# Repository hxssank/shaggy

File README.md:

# Shaggy

A physical music controller built around Raspberry Pi Pico 2. Nine Hall-sensor tiles bring individual audio stems in and out of a mix. A rotary control handles volume and library selection, and a small LCD shows the current bank and active stems.

The player starts all voices under a paused I2S stream, changes gains during playback, and admits a cached bank only after WAV and hash checks. [The engineering walkthrough](ENGINEERING.md) traces playback timing and the separate recovery bank.

This repository contains CircuitPython firmware, host-side preparation and installation tools, tests, and a KiCad carrier-board design. Audio recordings and device-specific backups are excluded.

## Open the carrier-board files

| File | Contents |
| --- | --- |
| [Schematic PDF](hardware/pcb/reports/schematic.pdf) and [KiCad schematic](hardware/pcb/shaggy-carrier.kicad_sch) | Pico, Hall-sensor, display, DAC and microSD connections |
| [KiCad board](hardware/pcb/shaggy-carrier.kicad_pcb) and [top view](hardware/pcb/preview/shaggy-top.png) | 100 x 80 mm revision A carrier |
| [Board STEP](hardware/pcb/shaggy-carrier.step) and [3D view](hardware/pcb/preview/shaggy-3d.png) | Carrier geometry for mechanical review |
| [BOM](hardware/pcb/bom.csv) | Component references, quantities and footprints |
| [Cable pinout](hardware/pcb/cable-pinout.csv) | Connector pin numbers, nets and wire labels |
| [Gerbers and drills](hardware/pcb/fabrication-prototype/) | Revision A prototype fabrication exports |
| [DRC report](hardware/pcb/reports/pcb-drc.json) | Current board check, including the configured exclusions |

KiCad 10.0.7 reported zero violations, unconnected items or schematic-parity issues on November 9. The report lists six disabled checks, including missing courtyards and footprint-filter mismatches. Review those exclusions and the actual module pinouts before ordering a PCB. No fabricated carrier test is recorded.

## What works in the code

- Nine stem controls with time-based fades and debounced sensor state.
- SD-card libraries with validated manifests and up to 64 banks.
- Flash caching before playback, so active voices do not compete with the display for SD bandwidth.
- An internal House-bank recovery path when the SD card or library fails.
- Volume takeover, hold gestures and a library picker on a 240 x 280 display.
- Staged installation with file hashes, readback checks, backups and rollback paths.

```mermaid
flowchart LR
  Tiles[Hall-sensor tiles] --> Control[Stem and volume control]
  Knob[Rotary control] --> Control
  SD[SD library] --> Manifest[Manifest validation]
  Manifest --> Cache[Selected-bank flash cache]
  Cache --> Player[Nine-voice player]
  Control --> Player
  Player --> DAC[TLV320DAC3100 DAC]
  DAC --> Speaker[Speaker]
  Control --> Display[ST7789 display]
```

## Engineering decisions

The SD card and display share SPI. Loading a bank into flash before playback avoids asking that bus to sustain every audio stream while redrawing the UI. `bank_cache.py` verifies WAV structure and available space before activating a cached bank.

The installer treats partial writes as a failure. It stages replacements, verifies content, and retains the prior files until activation succeeds. The tests inject write and reconnect failures to check the rollback path.

## Source map

| Path | Responsibility |
| --- | --- |
| [`firmware/shaggy_os.py`](firmware/shaggy_os.py) | Library startup, selected bank, recovery and playback sessions |
| [`firmware/shaggy.py`](firmware/shaggy.py) | Pico GPIO, audio mixer and playback loop |
| [`firmware/bank_cache.py`](firmware/bank_cache.py) | Validated SD-to-flash bank caching |
| [`firmware/player_display.py`](firmware/player_display.py) | Bank, stem, volume and error display |
| [`tools/prepare_sd_library.py`](tools/prepare_sd_library.py) | WAV validation, resampling and aligned SD library output |
| [`tools/install_sd.py`](tools/install_sd.py) | Staged firmware/library deployment and recovery |
| [`hardware/pcb/`](hardware/pcb/) | Carrier-board sources, footprint definitions and design scripts |
| [`tests/`](tests/) | Host-side logic and failure-injection tests |

## Run the host tests

Use Python 3.13 or 3.14 and [uv](https://docs.astral.sh/uv/).

```sh
uv sync --group dev
uv run pytest -q
uv run ruff check firmware tools tests
```

The public source snapshot passed **568 tests on November 9, 2026**. Two optional resampling tests skipped because NumPy was absent from that environment. A separate carrier-board netlist suite passed 11 tests. Ruff passed for firmware, tools and tests. These tests use fake hardware interfaces; they do not establish timing or audio quality on a physical Pico.

## Hardware and audio setup

The implementation targets a Pico 2 running CircuitPython, a TLV320DAC3100 audio board, an ST7789 display, nine Hall sensors, a volume potentiometer and an SPI microSD reader. Pin assignments live in `firmware/shaggy.py`, `firmware/sd_storage.py` and `firmware/volume_test.py`. Confirm power rails and actual module pinouts before wiring.

Supply your own licensed audio. Each bank uses nine mono, 16-bit PCM WAV files with matching frame counts. The SD preparation path produces 22,050 Hz files and validates the bank before deployment. The runtime and tests do not require redistributing the original recordings.

Run `python tools/install_sd.py --help` before connecting a board. Device installation writes firmware and storage; the desktop test command above does not open a physical device.

## Current limits and next work

The carrier PCB is a prototype design. A passing software suite or KiCad check does not prove a fabricated board works. The next hardware checks are long-duration playback with all nine stems, bank changes under realistic card latency, power-cycle recovery and end-to-end wiring review.

The public suite excludes acceptance tests that depended on private audio recordings. General WAV, manifest, caching and installation tests generate their own fixtures.

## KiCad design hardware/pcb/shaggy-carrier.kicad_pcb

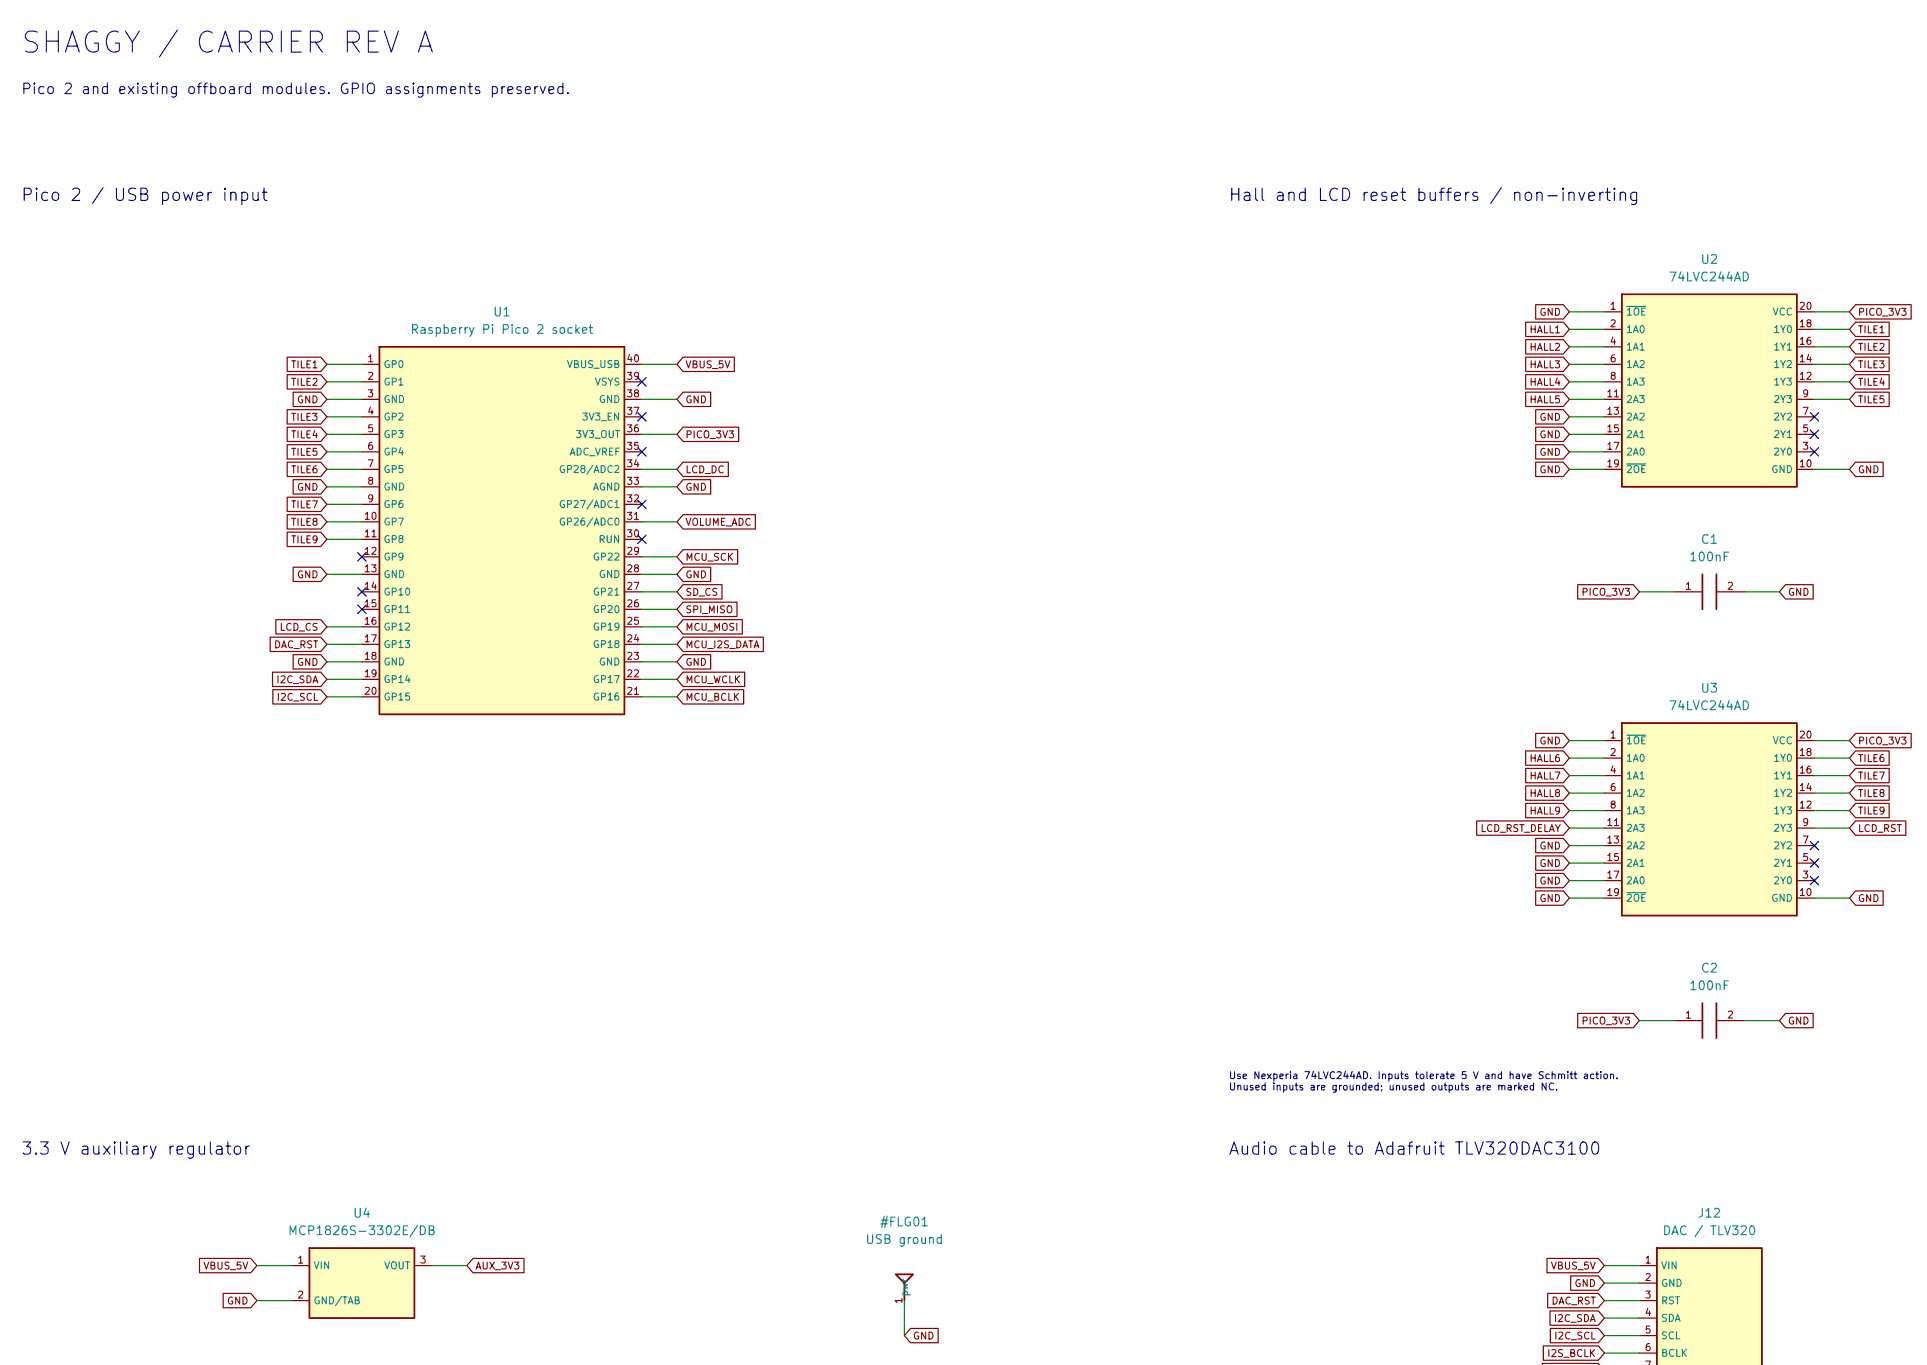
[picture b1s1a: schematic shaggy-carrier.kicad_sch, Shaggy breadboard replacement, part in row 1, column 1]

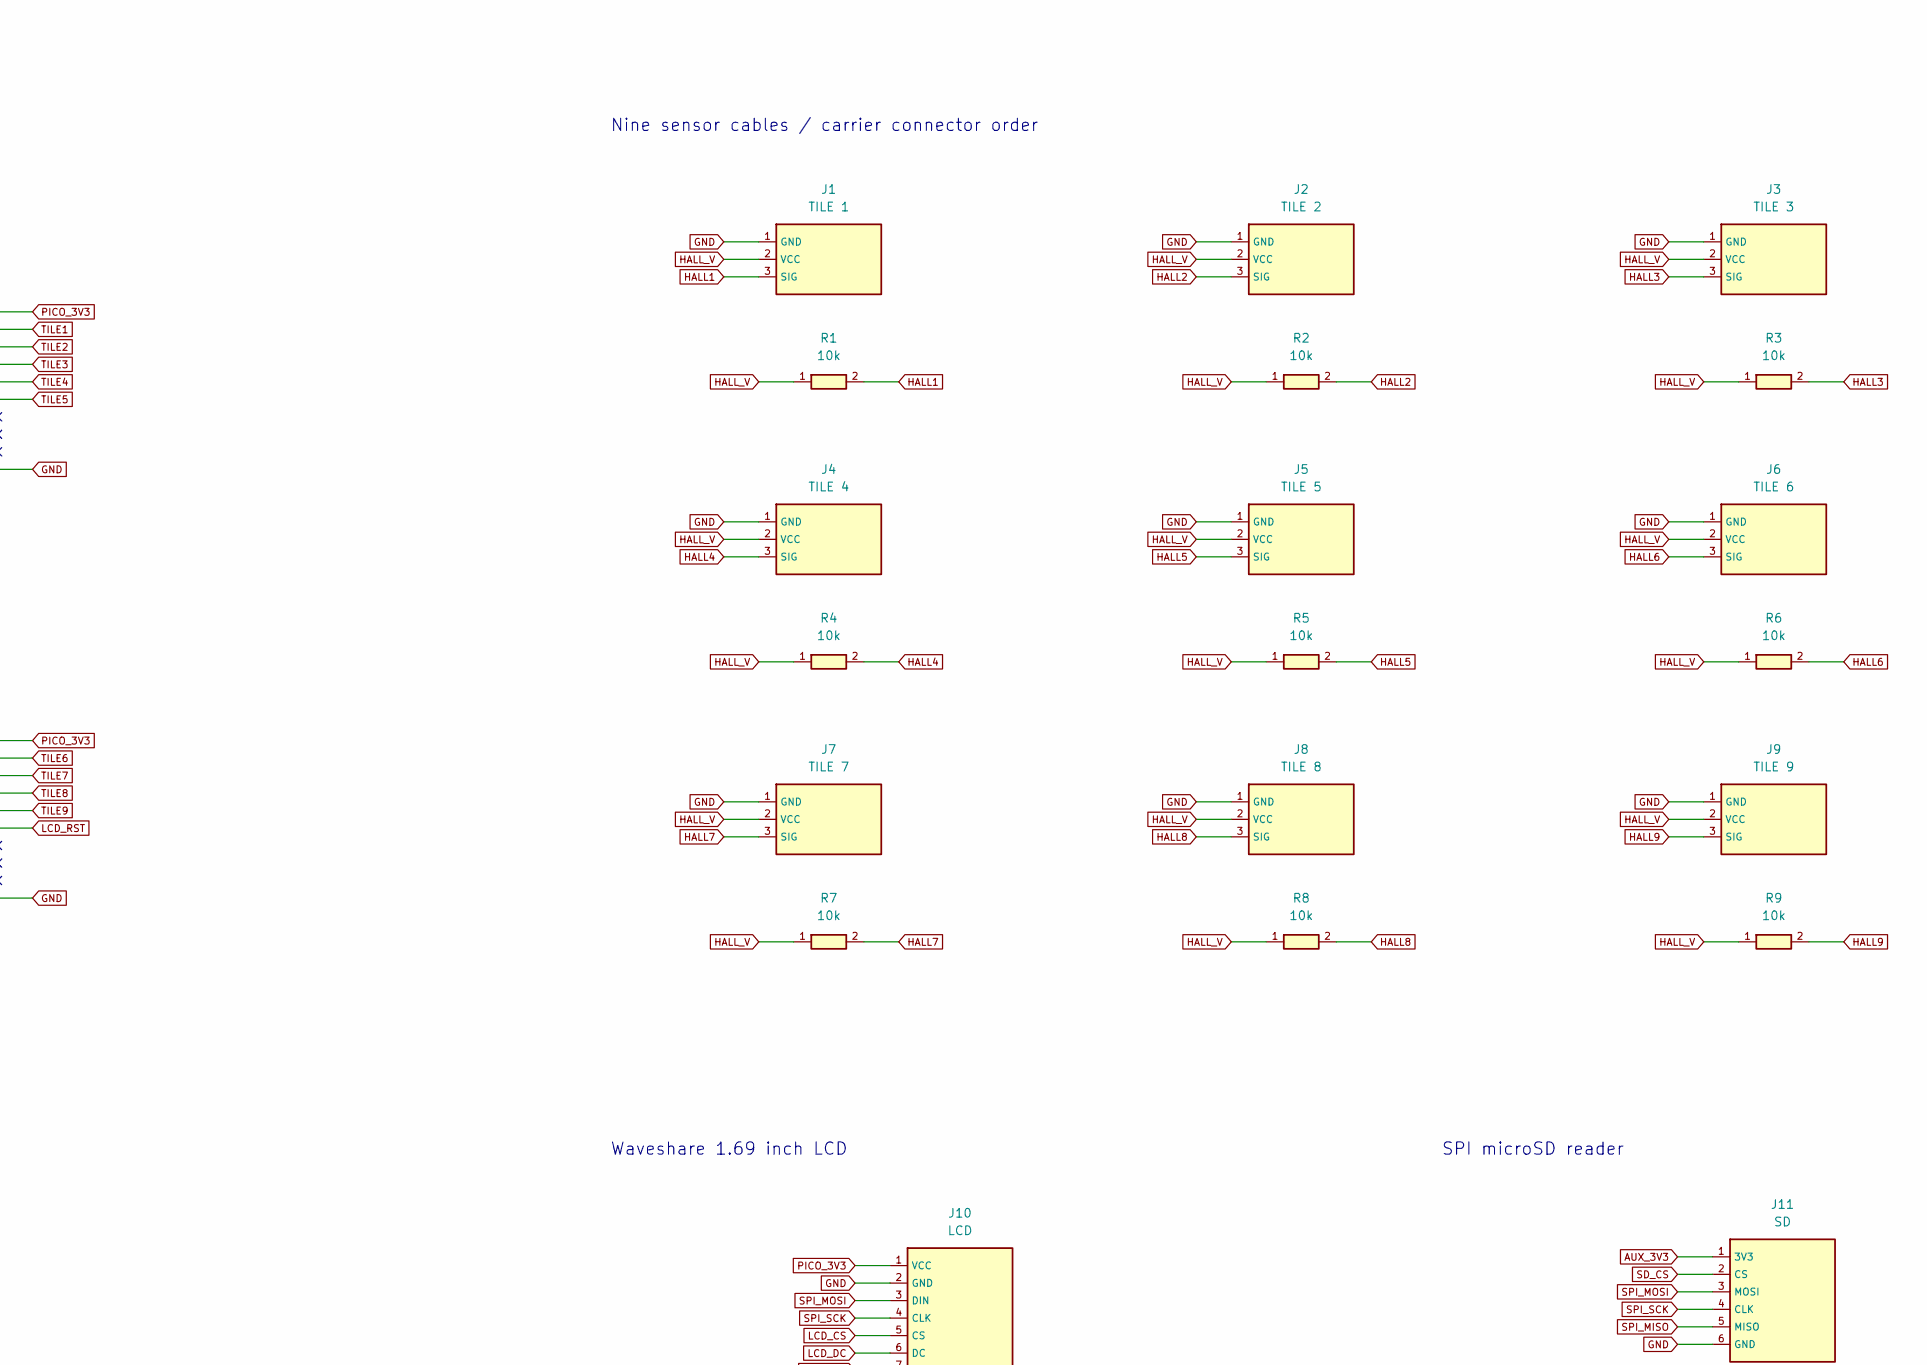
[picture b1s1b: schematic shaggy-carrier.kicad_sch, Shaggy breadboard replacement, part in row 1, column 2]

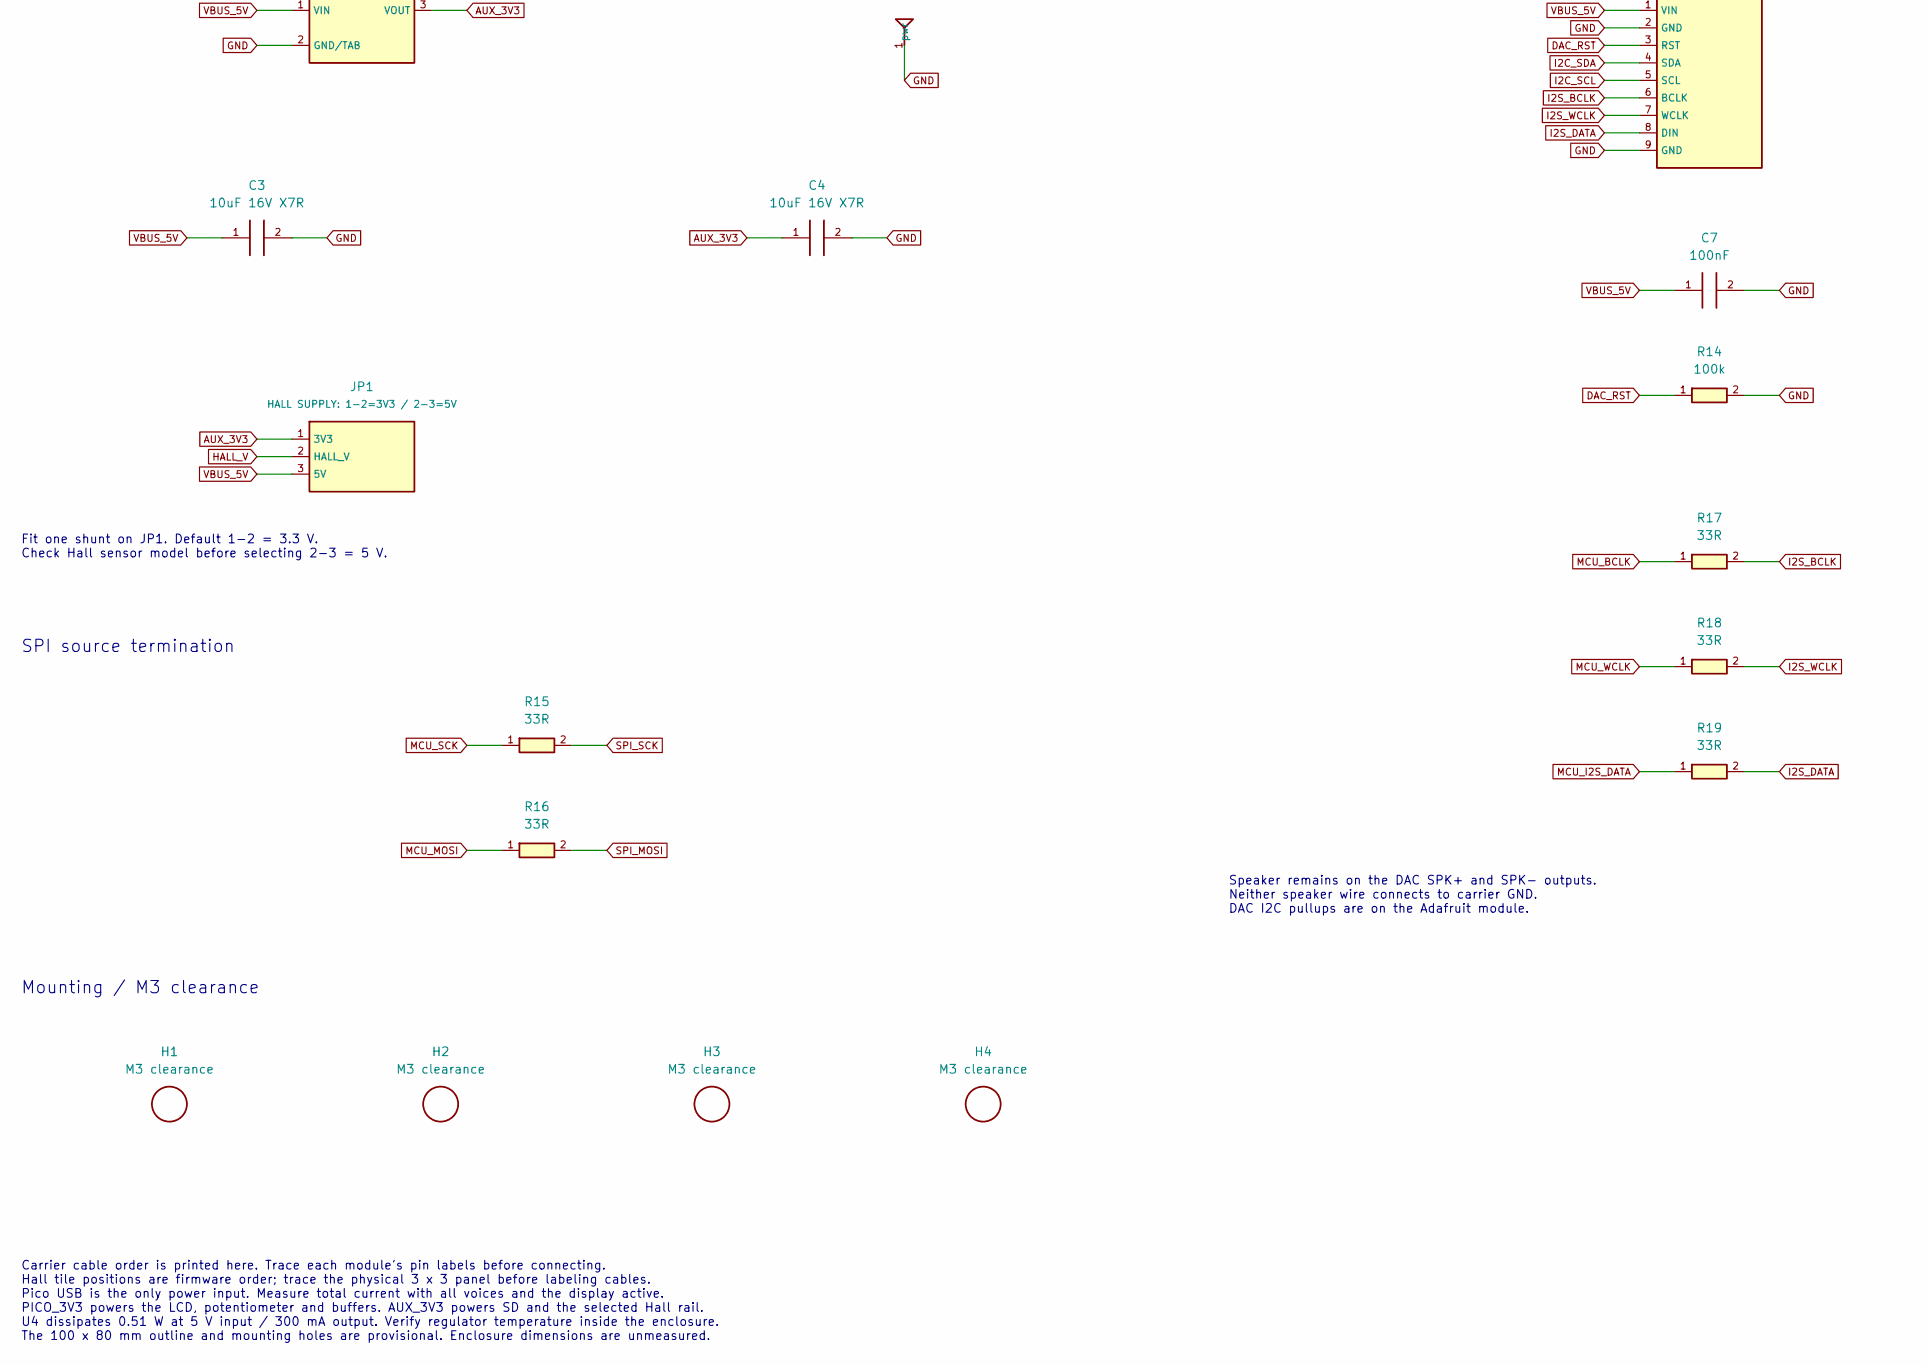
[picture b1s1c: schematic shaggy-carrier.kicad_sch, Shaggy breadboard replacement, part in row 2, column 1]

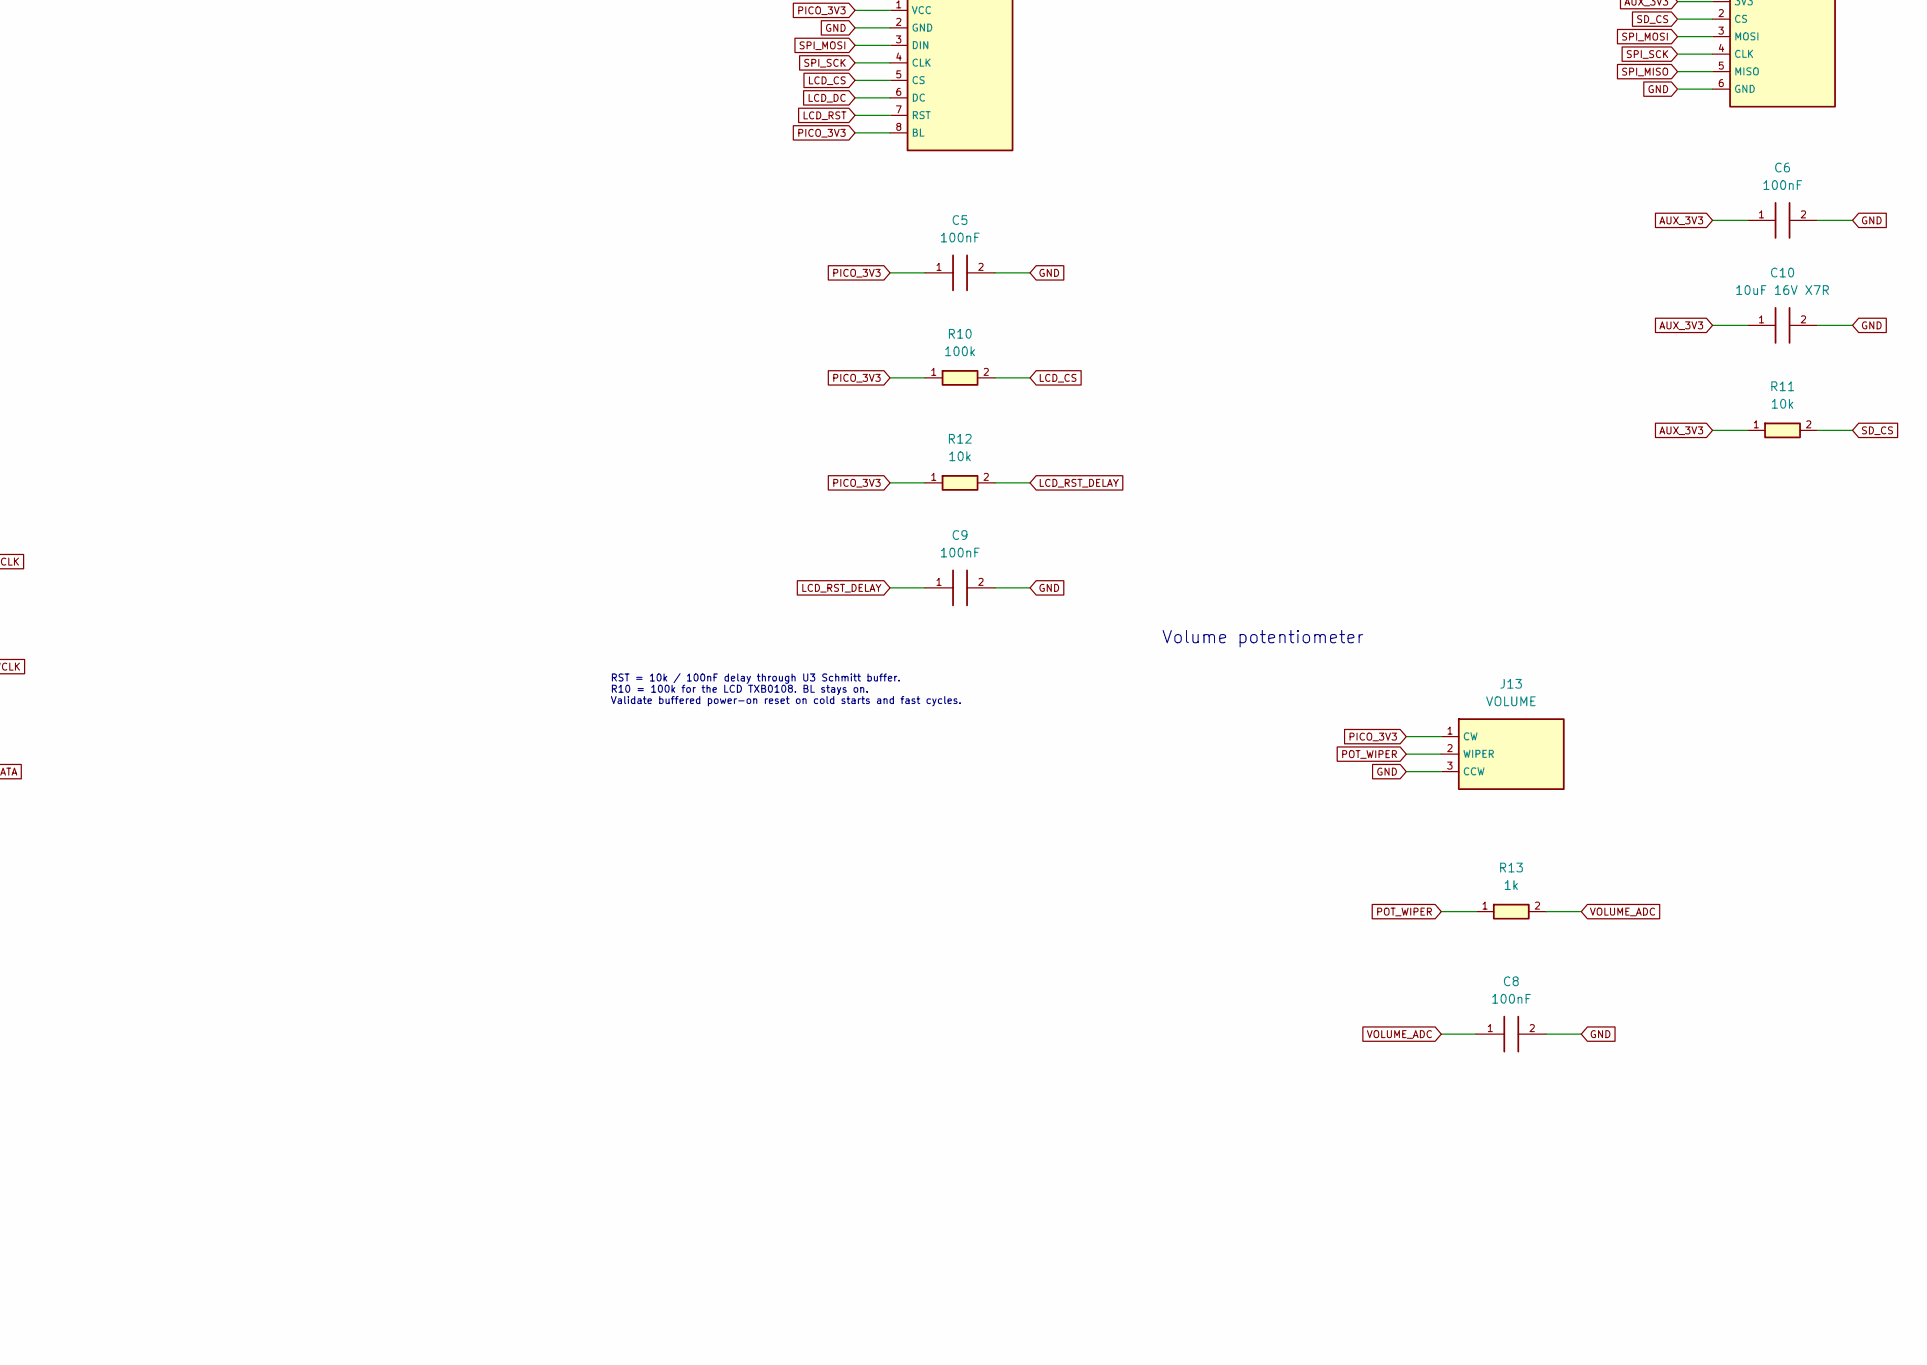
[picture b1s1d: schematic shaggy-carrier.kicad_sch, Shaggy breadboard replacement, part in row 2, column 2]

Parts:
C1, C2, C5, C6, C7, C8, C9: 100nF; C_0805_2012Metric
C3, C4, C10: 10uF 16V X7R; C_0805_2012Metric
H1, H2, H3, H4: M3 clearance; MountingHole_3.2mm_M3
J1: TILE 1; JST_XH_B3B-XH-A_1x03_P2.50mm_Vertical
J2: TILE 2; JST_XH_B3B-XH-A_1x03_P2.50mm_Vertical
J3: TILE 3; JST_XH_B3B-XH-A_1x03_P2.50mm_Vertical
J4: TILE 4; JST_XH_B3B-XH-A_1x03_P2.50mm_Vertical
J5: TILE 5; JST_XH_B3B-XH-A_1x03_P2.50mm_Vertical
J6: TILE 6; JST_XH_B3B-XH-A_1x03_P2.50mm_Vertical
J7: TILE 7; JST_XH_B3B-XH-A_1x03_P2.50mm_Vertical
J8: TILE 8; JST_XH_B3B-XH-A_1x03_P2.50mm_Vertical
J9: TILE 9; JST_XH_B3B-XH-A_1x03_P2.50mm_Vertical
J10: LCD; JST_XH_B8B-XH-A_1x08_P2.50mm_Vertical
J11: SD; JST_XH_B6B-XH-A_1x06_P2.50mm_Vertical
J12: DAC / TLV320; JST_XH_B9B-XH-A_1x09_P2.50mm_Vertical
J13: VOLUME; JST_XH_B3B-XH-A_1x03_P2.50mm_Vertical
JP1: HALL SUPPLY: 1-2=3V3 / 2-3=5V; PinHeader_1x03_P2.54mm_Vertical
R1, R2, R3, R4, R5, R6, R7, R8, R9, R11, R12: 10k; R_0805_2012Metric
R10, R14: 100k; R_0805_2012Metric
R13: 1k; R_0805_2012Metric
R15, R16, R17, R18, R19: 33R; R_0805_2012Metric
U1: Raspberry Pi Pico 2 socket; RaspberryPi_Pico_Common_THT
U2, U3: 74LVC244AD; SOIC-20W_7.5x12.8mm_P1.27mm
U4: MCP1826S-3302E/DB; SOT-223-3_TabPin2

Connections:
AUX_3V3: C4.1, C6.1, C10.1, J11.1 (3V3), JP1.1 (3V3), R11.1, U4.3 (VOUT)
DAC_RST: J12.3 (RST), R14.1, U1.17 (GP13)
GND: C1.2, C2.2, C3.2, C4.2, C5.2, C6.2, C7.2, C8.2, C9.2, C10.2, J1.1 (GND), J2.1 (GND), J3.1 (GND), J4.1 (GND), J5.1 (GND), J6.1 (GND), J7.1 (GND), J8.1 (GND), J9.1 (GND), J10.2 (GND), J11.6 (GND), J12.2 (GND), J12.9 (GND), J13.3 (CCW), R14.2, U1.3 (GND), U1.8 (GND), U1.13 (GND), U1.18 (GND), U1.23 (GND), U1.28 (GND), U1.33 (AGND), U1.38 (GND), U2.1 (~1OE), U2.10 (GND), U2.13 (2A2), U2.15 (2A1), U2.17 (2A0), U2.19 (~2OE), U3.1 (~1OE), U3.10 (GND), U3.13 (2A2), U3.15 (2A1), U3.17 (2A0), U3.19 (~2OE), U4.2 (GND/TAB)
HALL1: J1.3 (SIG), R1.2, U2.2 (1A0)
HALL2: J2.3 (SIG), R2.2, U2.4 (1A1)
HALL3: J3.3 (SIG), R3.2, U2.6 (1A2)
HALL4: J4.3 (SIG), R4.2, U2.8 (1A3)
HALL5: J5.3 (SIG), R5.2, U2.11 (2A3)
HALL6: J6.3 (SIG), R6.2, U3.2 (1A0)
HALL7: J7.3 (SIG), R7.2, U3.4 (1A1)
HALL8: J8.3 (SIG), R8.2, U3.6 (1A2)
HALL9: J9.3 (SIG), R9.2, U3.8 (1A3)
HALL_V: J1.2 (VCC), J2.2 (VCC), J3.2 (VCC), J4.2 (VCC), J5.2 (VCC), J6.2 (VCC), J7.2 (VCC), J8.2 (VCC), J9.2 (VCC), JP1.2 (HALL_V), R1.1, R2.1, R3.1, R4.1, R5.1, R6.1, R7.1, R8.1, R9.1
I2C_SCL: J12.5 (SCL), U1.20 (GP15)
I2C_SDA: J12.4 (SDA), U1.19 (GP14)
I2S_BCLK: J12.6 (BCLK), R17.2
I2S_DATA: J12.8 (DIN), R19.2
I2S_WCLK: J12.7 (WCLK), R18.2
LCD_CS: J10.5 (CS), R10.2, U1.16 (GP12)
LCD_DC: J10.6 (DC), U1.34 (GP28/ADC2)
LCD_RST: J10.7 (RST), U3.9 (2Y3)
LCD_RST_DELAY: C9.1, R12.2, U3.11 (2A3)
MCU_BCLK: R17.1, U1.21 (GP16)
MCU_I2S_DATA: R19.1, U1.24 (GP18)
MCU_MOSI: R16.1, U1.25 (GP19)
MCU_SCK: R15.1, U1.29 (GP22)
MCU_WCLK: R18.1, U1.22 (GP17)
PICO_3V3: C1.1, C2.1, C5.1, J10.1 (VCC), J10.8 (BL), J13.1 (CW), R10.1, R12.1, U1.36 (3V3_OUT), U2.20 (VCC), U3.20 (VCC)
POT_WIPER: J13.2 (WIPER), R13.1
SD_CS: J11.2 (CS), R11.2, U1.27 (GP21)
SPI_MISO: J11.5 (MISO), U1.26 (GP20)
SPI_MOSI: J10.3 (DIN), J11.3 (MOSI), R16.2
SPI_SCK: J10.4 (CLK), J11.4 (CLK), R15.2
TILE1: U1.1 (GP0), U2.18 (1Y0)
TILE2: U1.2 (GP1), U2.16 (1Y1)
TILE3: U1.4 (GP2), U2.14 (1Y2)
TILE4: U1.5 (GP3), U2.12 (1Y3)
TILE5: U1.6 (GP4), U2.9 (2Y3)
TILE6: U1.7 (GP5), U3.18 (1Y0)
TILE7: U1.9 (GP6), U3.16 (1Y1)
TILE8: U1.10 (GP7), U3.14 (1Y2)
TILE9: U1.11 (GP8), U3.12 (1Y3)
VBUS_5V: C3.1, C7.1, J12.1 (VIN), JP1.3 (5V), U1.40 (VBUS_USB), U4.1 (VIN)
VOLUME_ADC: C8.1, R13.2, U1.31 (GP26/ADC0)

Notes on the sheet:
SHAGGY / CARRIER REV A
Pico 2 and existing offboard modules. GPIO assignments preserved.
Pico 2 / USB power input
Hall and LCD reset buffers / non-inverting
Nine sensor cables / carrier connector order
3.3 V auxiliary regulator
Audio cable to Adafruit TLV320DAC3100
Waveshare 1.69 inch LCD
SPI microSD reader
Volume potentiometer
SPI source termination
Mounting / M3 clearance
Fit one shunt on JP1. Default 1-2 = 3.3 V. Check Hall sensor model before selecting 2-3 = 5 V.
Use Nexperia 74LVC244AD. Inputs tolerate 5 V and have Schmitt action. Unused inputs are grounded; unused outputs are marked NC.
Speaker remains on the DAC SPK+ and SPK- outputs. Neither speaker wire connects to carrier GND. DAC I2C pullups are on the Adafruit module.
RST = 10k / 100nF delay through U3 Schmitt buffer. R10 = 100k for the LCD TXB0108. BL stays on. Validate buffered power-on reset on cold starts and fast cycles.
Carrier cable order is printed here. Trace each module's pin labels before connecting. Hall tile positions are firmware order; trace the physical 3 x 3 panel before labeling cables. Pico USB is the only power input. Measure total current with all voices and the display active. PICO_3V3 powers the L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

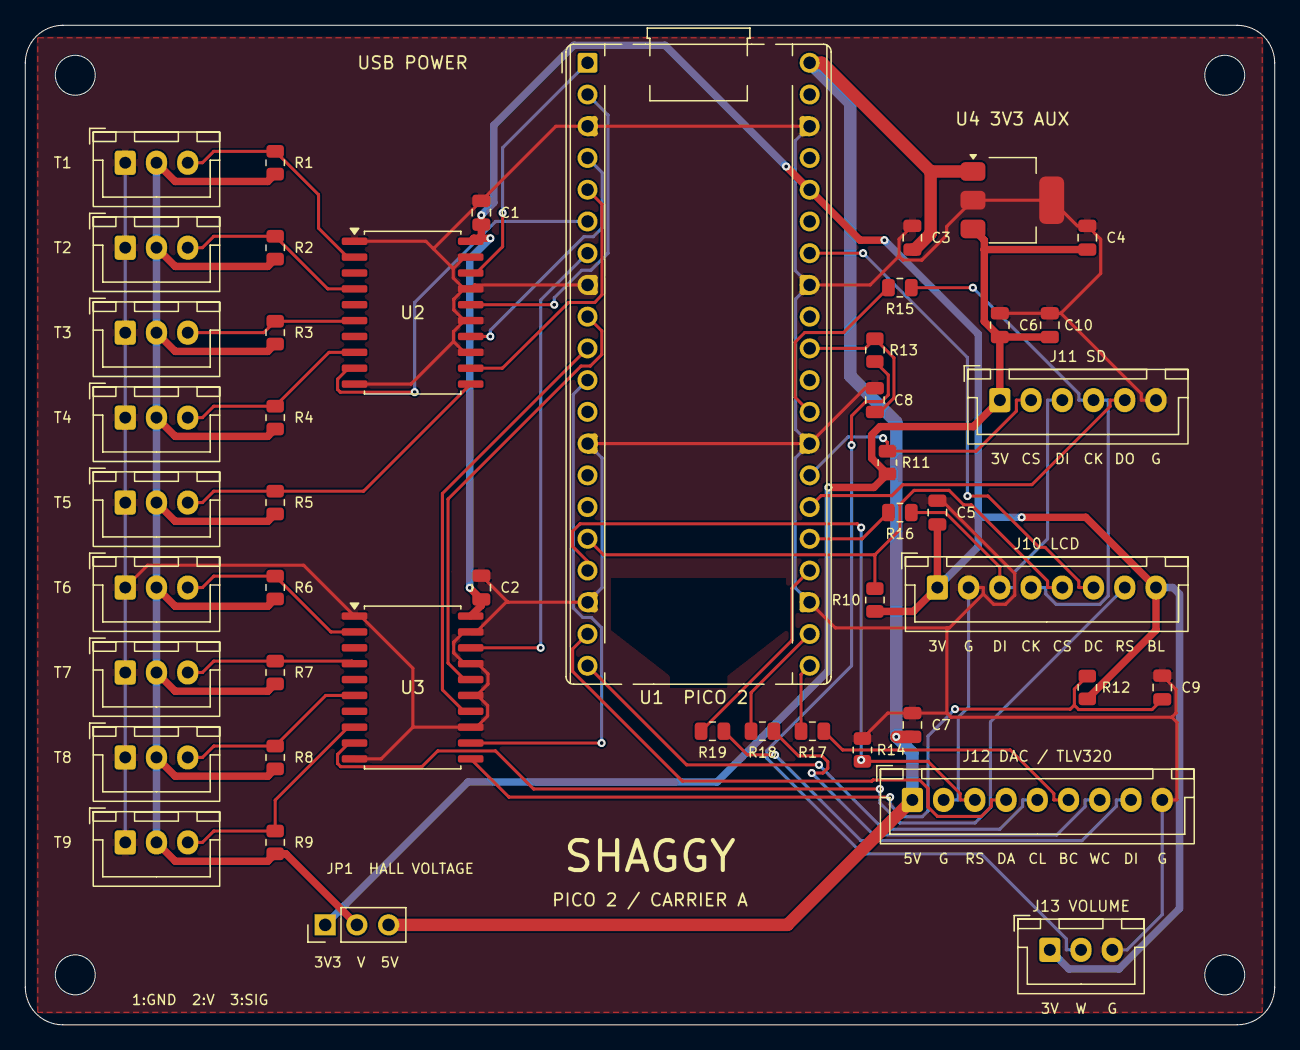
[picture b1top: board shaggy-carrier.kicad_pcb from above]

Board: 2 copper layers, 100.0 x 80.0 mm, 51 parts (0 on the bottom side), 44 nets.

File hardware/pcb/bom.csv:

Reference,Quantity,Value,Footprint or assembly part,Assembly note
U1,1,Raspberry Pi Pico 2 socket,Module:RaspberryPi_Pico_Common_THT,Reuse existing Pico 2; fit two 1x20 sockets
J1,1,TILE 1,Connector_JST:JST_XH_B3B-XH-A_1x03_P2.50mm_Vertical,
R1,1,10k,Resistor_SMD:R_0805_2012Metric,
J2,1,TILE 2,Connector_JST:JST_XH_B3B-XH-A_1x03_P2.50mm_Vertical,
R2,1,10k,Resistor_SMD:R_0805_2012Metric,
J3,1,TILE 3,Connector_JST:JST_XH_B3B-XH-A_1x03_P2.50mm_Vertical,
R3,1,10k,Resistor_SMD:R_0805_2012Metric,
J4,1,TILE 4,Connector_JST:JST_XH_B3B-XH-A_1x03_P2.50mm_Vertical,
R4,1,10k,Resistor_SMD:R_0805_2012Metric,
J5,1,TILE 5,Connector_JST:JST_XH_B3B-XH-A_1x03_P2.50mm_Vertical,
R5,1,10k,Resistor_SMD:R_0805_2012Metric,
J6,1,TILE 6,Connector_JST:JST_XH_B3B-XH-A_1x03_P2.50mm_Vertical,
R6,1,10k,Resistor_SMD:R_0805_2012Metric,
J7,1,TILE 7,Connector_JST:JST_XH_B3B-XH-A_1x03_P2.50mm_Vertical,
R7,1,10k,Resistor_SMD:R_0805_2012Metric,
J8,1,TILE 8,Connector_JST:JST_XH_B3B-XH-A_1x03_P2.50mm_Vertical,
R8,1,10k,Resistor_SMD:R_0805_2012Metric,
J9,1,TILE 9,Connector_JST:JST_XH_B3B-XH-A_1x03_P2.50mm_Vertical,
R9,1,10k,Resistor_SMD:R_0805_2012Metric,
U2,1,74LVC244AD,Package_SO:SOIC-20W_7.5x12.8mm_P1.27mm,Nexperia 74LVC244AD; Schmitt inputs required
U3,1,74LVC244AD,Package_SO:SOIC-20W_7.5x12.8mm_P1.27mm,Nexperia 74LVC244AD; Schmitt inputs required
C1,1,100nF,Capacitor_SMD:C_0805_2012Metric,
C2,1,100nF,Capacitor_SMD:C_0805_2012Metric,
JP1,1,HALL SUPPLY: 1-2=3V3 / 2-3=5V,Connector_PinHeader_2.54mm:PinHeader_1x03_P2.54mm_Vertical,Fit one shunt only; default pins 1-2 for 3.3V
U4,1,MCP1826S-3302E/DB,Package_TO_SOT_SMD:SOT-223-3_TabPin2,
C3,1,10uF 16V X7R,Capacitor_SMD:C_0805_2012Metric,X7R +/-10%; select part with at least 1uF effective at operating bias and temperature
C4,1,10uF 16V X7R,Capacitor_SMD:C_0805_2012Metric,X7R +/-10%; select part with at least 1uF effective at operating bias and temperature
J10,1,LCD,Connector_JST:JST_XH_B8B-XH-A_1x08_P2.50mm_Vertical,
J11,1,SD,Connector_JST:JST_XH_B6B-XH-A_1x06_P2.50mm_Vertical,
J12,1,DAC / TLV320,Connector_JST:JST_XH_B9B-XH-A_1x09_P2.50mm_Vertical,
J13,1,VOLUME,Connector_JST:JST_XH_B3B-XH-A_1x03_P2.50mm_Vertical,
C5,1,100nF,Capacitor_SMD:C_0805_2012Metric,
C6,1,100nF,Capacitor_SMD:C_0805_2012Metric,
C7,1,100nF,Capacitor_SMD:C_0805_2012Metric,
C8,1,100nF,Capacitor_SMD:C_0805_2012Metric,
C9,1,100nF,Capacitor_SMD:C_0805_2012Metric,
C10,1,10uF 16V X7R,Capacitor_SMD:C_0805_2012Metric,X7R +/-10%; select part with at least 1uF effective at operating bias and temperature
R10,1,100k,Resistor_SMD:R_0805_2012Metric,
R11,1,10k,Resistor_SMD:R_0805_2012Metric,
R12,1,10k,Resistor_SMD:R_0805_2012Metric,
R13,1,1k,Resistor_SMD:R_0805_2012Metric,
R14,1,100k,Resistor_SMD:R_0805_2012Metric,
R15,1,33R,Resistor_SMD:R_0805_2012Metric,
R16,1,33R,Resistor_SMD:R_0805_2012Metric,
R17,1,33R,Resistor_SMD:R_0805_2012Metric,
R18,1,33R,Resistor_SMD:R_0805_2012Metric,
R19,1,33R,Resistor_SMD:R_0805_2012Metric,
U1 sockets,2,"1x20 female socket, 2.54mm pitch",Through-hole,Match Pico header pin height
JP1 shunt,1,2.54mm 2-pin shunt,Removable,Default pins 1-2
Cable housings 3-way,10,JST XH 3-position mating housing,Cable assembly,Re-pin to carrier pinout; module wire order is not assumed
Cable housings 6-way,1,JST XH 6-position mating housing,Cable assembly,Re-pin to carrier pinout; module wire order is not assumed
Cable housings 8-way,1,JST XH 8-position mating housing,Cable assembly,Re-pin to carrier pinout; module wire order is not assumed
Cable housings 9-way,1,JST XH 9-position mating housing,Cable assembly,Re-pin to carrier pinout; module wire order is not assumed
Cable terminals,53,Matching JST XH crimp contacts,Cable assembly,Select contacts for the actual wire gauge

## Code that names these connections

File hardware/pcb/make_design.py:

import json
import uuid
from pathlib import Path

ROOT = Path(__file__).resolve().parent
NS = uuid.UUID("2f17a198-4b01-49cb-bf98-4cb90094d5b1")
components = []


def add(
    ref: str,
    value: str,
    footprint: str,
    pins: dict,
    x: float,
    y: float,
    angle: float = 0,
    **extra: object,
) -> None:
    components.append(
        dict(
            ref=ref,
            value=value,
            footprint=footprint,
            pins={str(k): v for k, v in pins.items()},
            x=x,
            y=y,
            angle=angle,
            uuid=str(uuid.uuid5(NS, ref)),
            **extra,
        )
    )


def passive(
    ref: str, value: str, a: str, b: str, x: float, y: float, angle: float = 0
) -> None:
    library = (
        "Resistor_SMD:R_0805_2012Metric"
        if ref.startswith("R")
        else "Capacitor_SMD:C_0805_2012Metric"
    )
    add(ref, value, library, {1: a, 2: b}, x, y, angle)


def connector(
    ref: str, value: str, nets: list, x: float, y: float, angle: float = 0
) -> None:
    n = len(nets)
    fp = f"Connector_JST:JST_XH_B{n}B-XH-A_1x{n:02d}_P2.50mm_Vertical"
    add(ref, value, fp, dict(enumerate(nets, 1)), x, y, angle)


pico = {
    1: "TILE1",
    2: "TILE2",
    3: "GND",
    4: "TILE3",
    5: "TILE4",
    6: "TILE5",
    7: "TILE6",
    8: "GND",
    9: "TILE7",
    10: "TILE8",
    11: "TILE9",
    12: None,
    13: "GND",
    14: None,
    15: None,
    16: "LCD_CS",
    17: "DAC_RST",
    18: "GND",
    19: "I2C_SDA",
    20: "I2C_SCL",
    21: "MCU_BCLK",
    22: "MCU_WCLK",
    23: "GND",
    24: "MCU_I2S_DATA",
    25: "MCU_MOSI",
    26: "SPI_MISO",
    27: "SD_CS",
    28: "GND",
    29: "MCU_SCK",
    30: None,
    31: "VOLUME_ADC",
    32: None,
    33: "GND",
    34: "LCD_DC",
    35: None,
    36: "PICO_3V3",
    37: None,
    38: "GND",
    39: None,
    40: "VBUS_5V",
}
add(
    "U1",
    "Raspberry Pi Pico 2 socket",
    "Module:RaspberryPi_Pico_Common_THT",
    pico,
    45,
    3,
    datasheet="https://datasheets.raspberrypi.com/pico/pico-2-datasheet.pdf",
)
for i in range(1, 10):
    connector(
        f"J{i}", f"TILE {i}", ["GND", "HALL_V", f"HALL{i}"], 8, 11 + (i - 1) * 6.8
    )
    passive(f"R{i}", "10k", "HALL_V", f"HALL{i}", 20, 11 + (i - 1) * 6.8, 90)

inputs = [2, 4, 6, 8, 11, 13, 15, 17]
outputs = [18, 16, 14, 12, 9, 7, 5, 3]
for chip, count, offset, y in [("U2", 5, 0, 23), ("U3", 4, 5, 53)]:
    pins = {1: "GND", 19: "GND", 10: "GND", 20: "PICO_3V3"}
    for index, (a, z) in enumerate(zip(inputs, outputs)):
        pins[a] = f"HALL{offset + index + 1}" if index < count else "GND"
        pins[z] = f"TILE{offset + index + 1}" if index < count else None
    if chip == "U3":
        pins[11] = "LCD_RST_DELAY"
        pins[9] = "LCD_RST"
    add(
        chip,
        "74LVC244AD",
        "Package_SO:SOIC-20W_7.5x12.8mm_P1.27mm",
        pins,
        31,
        y,
        datasheet="https://assets.nexperia.com/documents/data-sheet/74LVC_LVCH244A.pdf",
    )
passive("C1", "100nF", "PICO_3V3", "GND", 36.5, 15, 90)
passive("C2", "100nF", "PICO_3V3", "GND", 36.5, 45, 90)
add(
    "JP1",
    "HALL SUPPLY: 1-2=3V3 / 2-3=5V",
    "Connector_PinHeader_2.54mm:PinHeader_1x03_P2.54mm_Vertical",
    {1: "AUX_3V3", 2: "HALL_V", 3: "VBUS_5V"},
    24,
    72,
    90,
)

add(
    "U4",
    "MCP1826S-3302E/DB",
    "Package_TO_SOT_SMD:SOT-223-3_TabPin2",
    {1: "VBUS_5V", 2: "GND", 3: "AUX_3V3"},
    79,
    14,
    datasheet="https://ww1.microchip.com/downloads/en/DeviceDoc/22057B.pdf",
)
passive("C3", "10uF 16V X7R", "VBUS_5V", "GND", 71, 17, 90)
passive("C4", "10uF 16V X7R", "AUX_3V3", "GND", 85, 17, 90)
connector(
    "J10",
    "LCD",
    [
        "PICO_3V3",
        "GND",
        "SPI_MOSI",
        "SPI_SCK",
        "LCD_CS",
        "LCD_DC",
        "LCD_RST",
        "PICO_3V3",
    ],
    73,
    45,
)
connector(
    "J11", "SD", ["AUX_3V3", "SD_CS", "SPI_MOSI", "SPI_SCK", "SPI_MISO", "GND"], 78, 30
)
connector(
    "J12",
    "DAC / TLV320",
    [
        "VBUS_5V",
        "GND",
        "DAC_RST",
        "I2C_SDA",
        "I2C_SCL",
        "I2S_BCLK",
        "I2S_WCLK",
        "I2S_DATA",
        "GND",
    ],
    71,
    62,
)
connector("J13", "VOLUME", ["PICO_3V3", "POT_WIPER", "GND"], 82, 74)
passive("C5", "100nF", "PICO_3V3", "GND", 73, 39, 90)
passive("C6", "100nF", "AUX_3V3", "GND", 78, 24, 90)
passive("C7", "100nF", "VBUS_5V", "GND", 71, 56, 90)
passive("C8", "100nF", "VOLUME_ADC", "GND", 68, 30, 90)
passive("C9", "100nF", "LCD_RST_DELAY", "GND", 91, 53, 90)
passive("C10", "10uF 16V X7R", "AUX_3V3", "GND", 82, 24, 90)
passive("R10", "100k", "PICO_3V3", "LCD_CS", 68, 46, 90)
passive("R11", "10k", "AUX_3V3", "SD_CS", 69, 35, 90)
passive("R12", "10k", "PICO_3V3", "LCD_RST_DELAY", 85, 53, 90)
passive("R13", "1k", "POT_WIPER", "VOLUME_ADC", 68, 26, 90)
passive("R14", "100k", "DAC_RST", "GND", 67, 58, 90)
for ref, a, b, x, y in [
    ("R15", "MCU_SCK", "SPI_SCK", 70, 21),
    ("R16", "MCU_MOSI", "SPI_MOSI", 70, 39),
    ("R17", "MCU_BCLK", "I2S_BCLK", 63, 56.5),
    ("R18", "MCU_WCLK", "I2S_WCLK", 59, 56.5),
    ("R19", "MCU_I2S_DATA", "I2S_DATA", 55, 56.5),
]:
    passive(ref, "33R", a, b, x, y)
for i, (x, y) in enumerate([(4, 4), (96, 4), (4, 76), (96, 76)], 1):
    add(f"H{i}", "M3 clearance", "MountingHole:MountingHole_3.2mm_M3", {}, x, y)

data = dict(
    name="shaggy-carrier",
    revision="A - prototype",
    width=100,
    height=80,
    root_uuid=str(uuid.uuid5(NS, "root")),
    components=components,
    notes=[
        "100 x 80 mm outline is provisional; enclosure fit is unmeasured.",
        "Pico USB is the only power input. "
        "Use a suitable 5 V supply; measure total current.",
        "J1-J9: 1=GND, 2=HALL_V, 3=signal. Verify actual sensor pin order.",
        "JP1: fit ONE shunt, default 1-2 for 3.3 V. Check sensor rating before 5 V.",
        "Buffers require Nexperia 74LVC244AD with 5 V tolerant Schmitt inputs.",
        "Speaker stays wired to DAC SPK+ and SPK-. Neither wire connects to GND.",
        "LCD RST uses buffered 10k/100nF power-on reset; "
        "BL is always on. Validate cold starts.",
        "Pico3V3 powers LCD, pot and buffers. "
        "AUX3V3 powers SD and selectable Hall rail.",
        "U4 loss at 5 V input is 0.51 W at 300 mA; verify temperature in enclosure.",
        "Connector order is the carrier order; build labeled adapter cables.",
        "Firmware GPIO assignment preserved. Tile physical order must be traced.",
    ],
)
(ROOT / "design.json").write_text(json.dumps(data, indent=2) + "\n")

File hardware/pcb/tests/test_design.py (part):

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        ref, output = matches[0]
        assert pin_net(ref, output) == gpio_net(gpio)
        assert pin_net(f"J{index}", 1) == "GND"
        assert pin_net(f"J{index}", 2) == pin_net("JP1", 2) == "HALL_V"
        assert pin_net(f"R{index}", 1) == "HALL_V"
        assert pin_net(f"R{index}", 2) == sensor_net


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    assert COMPONENTS[ref].findtext("footprint") == (
        "Package_SO:SOIC-20W_7.5x12.8mm_P1.27mm"
    )
    assert pin_net(ref, 20) == pin_net("U1", 36) == "PICO_3V3"
    assert {pin_net(ref, number) for number in (1, 10, 19)} == {"GND"}
    for input_pin, output_pin in BUFFER_PAIRS.items():
        if pin_net(ref, output_pin).startswith("unconnected-"):
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
def test_potentiometer_reaches_firmware_adc_through_filter() -> None:
    adc = call("shaggy.py", "analogio", "AnalogIn")
    assert pin_net("J13", 1) == "PICO_3V3"
    assert pin_net("J13", 3) == "GND"
    assert pin_net("J13", 2) == pin_net("R13", 1)
    assert pin_net("R13", 2) == gpio_net(board_gpio(adc.args[0]))
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    assert COMPONENTS["U4"].findtext("footprint") == (
        "Package_TO_SOT_SMD:SOT-223-3_TabPin2"
    )
    assert pin_net("U4", 1) == pin_net("U1", 40) == "VBUS_5V"
    assert pin_net("U4", 2) == "GND"
    assert pin_net("U4", 3) == "AUX_3V3"
    rails = {pin_net("U1", 36), pin_net("U1", 40), pin_net("U4", 3), "GND"}
    assert len(rails) == 4
    for net in XML.findall("./nets/net"):
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            if node.attrib["pintype"] == "power_out"
        ]
        assert len(sources) == 1, net.attrib["name"]
    assert pin_net("JP1", 1) == "AUX_3V3"
    assert pin_net("JP1", 3) == "VBUS_5V"
    assert pin_net("J10", 1) == pin_net("J10", 8) == "PICO_3V3"
    assert pin_net("J11", 1) == "AUX_3V3"
    assert pin_net("J12", 1) == "VBUS_5V"
    assert pin_net("C3", 1) == "VBUS_5V"
    assert pin_net("C4", 1) == "AUX_3V3"
    assert pin_net("C3", 2) == pin_net("C4", 2) == "GND"


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    assert delay == pin_net("C9", 1) == pin_net("U3", 11)
    assert pin_net("U3", BUFFER_PAIRS[11]) == pin_net("J10", 7)
    assert delay != pin_net("J10", 7)
    assert pin_net("R12", 1) == "PICO_3V3"
    assert pin_net("C9", 2) == "GND"
    assert COMPONENTS["R12"].findtext("value") == "10k"
    assert COMPONENTS["C9"].findtext("value") == "100nF"
    assert COMPONENTS["R10"].findtext("value") == "100k"
    assert pin_net("R10", 1) == "PICO_3V3"
    assert pin_net("R10", 2) == pin_net("J10", 5)


def test_sd_cs_pullup_uses_card_supply() -> None:
    assert pin_net("R11", 1) == pin_net("J11", 1) == "AUX_3V3"
    assert pin_net("R11", 2) == pin_net("J11", 2)
    assert COMPONENTS["R11"].findtext("value") == "10k"

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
